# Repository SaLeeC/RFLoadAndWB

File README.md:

# RFLoadAndWB
A board to have a low power Variable Z Load and a RF Wheatstone Bridge

The intention is to make a small card (under 10 X 10 cm) that provides a dummy load (low power) with variable impedance between 5 and 2555 Ohm programmable in 5 Ohm steps and, at the same time, a Weathston Bridge which works in direct current and in RF to measure the unknown Z always in the range between 5 and 2555 Ohm.

The project is based on the following finished functional blocks:

a) Variable Z dummy load

b) Reference divider for the Weathston Bridge

c) Constant Current Generator

d) RF-DC converter for the measurement of the incoming Radio Frequency level

e) RF-DC converter for measuring the level of the reference Radio Frequency for the Weathston Bridge

f) RF-DC converter for measuring the level across the Unknown Impedance

g) Comparator for the comparison between the reference and the level at the ends of the Unknown Impedance

h) LED display for the representation of the board status (including the result of the comparison)

i) IIC interface for setting the operating parameters

All modules are finished units so they can be assembled, tested and used separately from each other.

For its operation, the board does not require a microcontroller, PC, software or other devilry, it only requires a series of switches or jumpers with which we can manually set all the operating parameters.

For the measurements a tester or a multimeter is sufficient because all the measured values are converted into Direct Current.

For direct current resistance measurements, the unknown resistor is powered by a 1 mA constant current pump allowing to read its value in Ohm directly in mV.

It is also possible to connect the card to a microcontroller through the interface module in IIC (I2C).

As for the measured values, these are converted into Direct Current and can assume values between 0 and 3.3V allowing easy interfacing with the Analog-Digital converters which are normally equipped with microcontrollers.

The comparator output is digital information and assumes the values of 0 or 3.3V

All the elements that make up the Dummy Load are 1W SMD resistors for which 1W is assumed as the maximum applicable power, in fact, since only the value of 10 Ohm is obtained with a single resistor, if really necessary, it will be possible to apply higher powers in function of the set value. This operation can irreversibly damage the load if during use combinations are chosen that are not able to withstand the applied power. In any case it is recommended not to apply more than 2W.

Inside the board hare present a free Op Amp with minimum circuit usable with Inp+ Inp- and Out for integration and experimental use

All schematics and PCB design are provided in KiCad format

The software is developed with Visual Studio Code through the PlatformIo App and is compatible with the "Arduino" environment

Mechanical drawings are produced with FreeCad.

# RFLoadAndWB
Una scheda che faccia da Carico Fittizio ad Impedenza Variabile e da Ponte di Weathston in RF

l'intenzione è quella di realizzare una piccola scheda (sotto i 10 X 10 cm) che fornisca un carico fittizio (bassa potenza) con impedenza variabile tra 5 e 2555 Ohm programmabile in step di 5 Ohm e, allo stesso tempo, un Weathston Bridge che funzioni in in corrente continua e in RF per misurare lo Z sconosciuto sempre nel range tra 5 e 2555 Ohm.

Il progetto è basato sui seguenti blocchi funzionali finiti:

a) Carico fittizio a Z variabile

b) Partitore di riferimento per il Ponte di Weathston

c) Generatore di Corrente Costante

d) Convertitore RF-DC per la misura del livello della Radio Frequenza in ingresso

e) Convertitore RF-DC per la misura del livello della Radio Frequenza di riferimento per il Ponte di Weathston

f) Convertitore RF-DC per la misura del livello ai capi della Impedenza Incognita

g) Comparatore per il confronto fra il riferimento e il livello ai capi della Impedenza Incognita

h) Display a LED per la rappresentazione dello stato della scheda (compreso il risultato della comparazione)

i) Interfaccia IIC per l'impostazione dei parametri di funzionamento

Tutti i moduli sono unità finite per cui possono essere assemblati, testati e usati separatamente uno dall'altro. 

Per il suo funzionamento la scheda non necessita di microcontrollore, PC, software o altre diavolerie, richiede solo una serie di interruttori o ponticelli con i quali possiamo manualmente impostare tutti i parametri di funzionamento.

Per le misure è sufficiente un tester o un multimetro perchè tutti i valori misurati sono convertiti in Corrente Continua.

Per le misure di resistenza in Corrente Continua la resistenza incognita è alimentata con una pompa di corrente costante da 1 mA permettendo di leggerne il valore in Ohm direttamente in mV.

E' altresì possibile collegare la scheda ad un microcontrollore tramite il modulo di interfacciamento in IIC (I2C).

Per quanto riguarda i valori misurati, questi sono convertiti in Corrente Continua e possono assumere valori compresi fra 0 e 3.3V permettendo un agevole interfacciamento con i convertitori Analogico Digitali di cui normalmente sono dotati i microcontrollori.

L'uscita del comparatore è una informazione digitale ed assume i valori di 0 o 3.3V

Tutti gli elementi che compongono il Carico Fittizio sono resistenze SMD da 1W per cui si assume 1W come potenza massima applicabile, in effetti, siccome solo il valore di 10 Ohm è ottenuto con una sola resistenza, se realmente necessario,sarà possibile applicare potenze maggiori  in funzione del valore impostato. Questa operazione può danneggiare irreversibilmente il carico se durante l'uso si scelgono combinazioni che non siano in grado di sopportare la potenza applicata. In ogni caso si consiglia di non applicare più di 2W.

All'interno della scheda è presente un Op Amp circuitato con i componenti minimi e utilizzabile tramite i pin Inp+ Inp- e Out, da usare per integrazioni o esperimenti.

Tutti gli schemi e il progetto del PCB sono forniti in formato KiCad

Il software è sviluppato con Visual Studio Code tramite l'App PlatformIo ed è compatibile con l'ambiente "Arduino"

I disegni meccanici sono prodotti con FreeCad.

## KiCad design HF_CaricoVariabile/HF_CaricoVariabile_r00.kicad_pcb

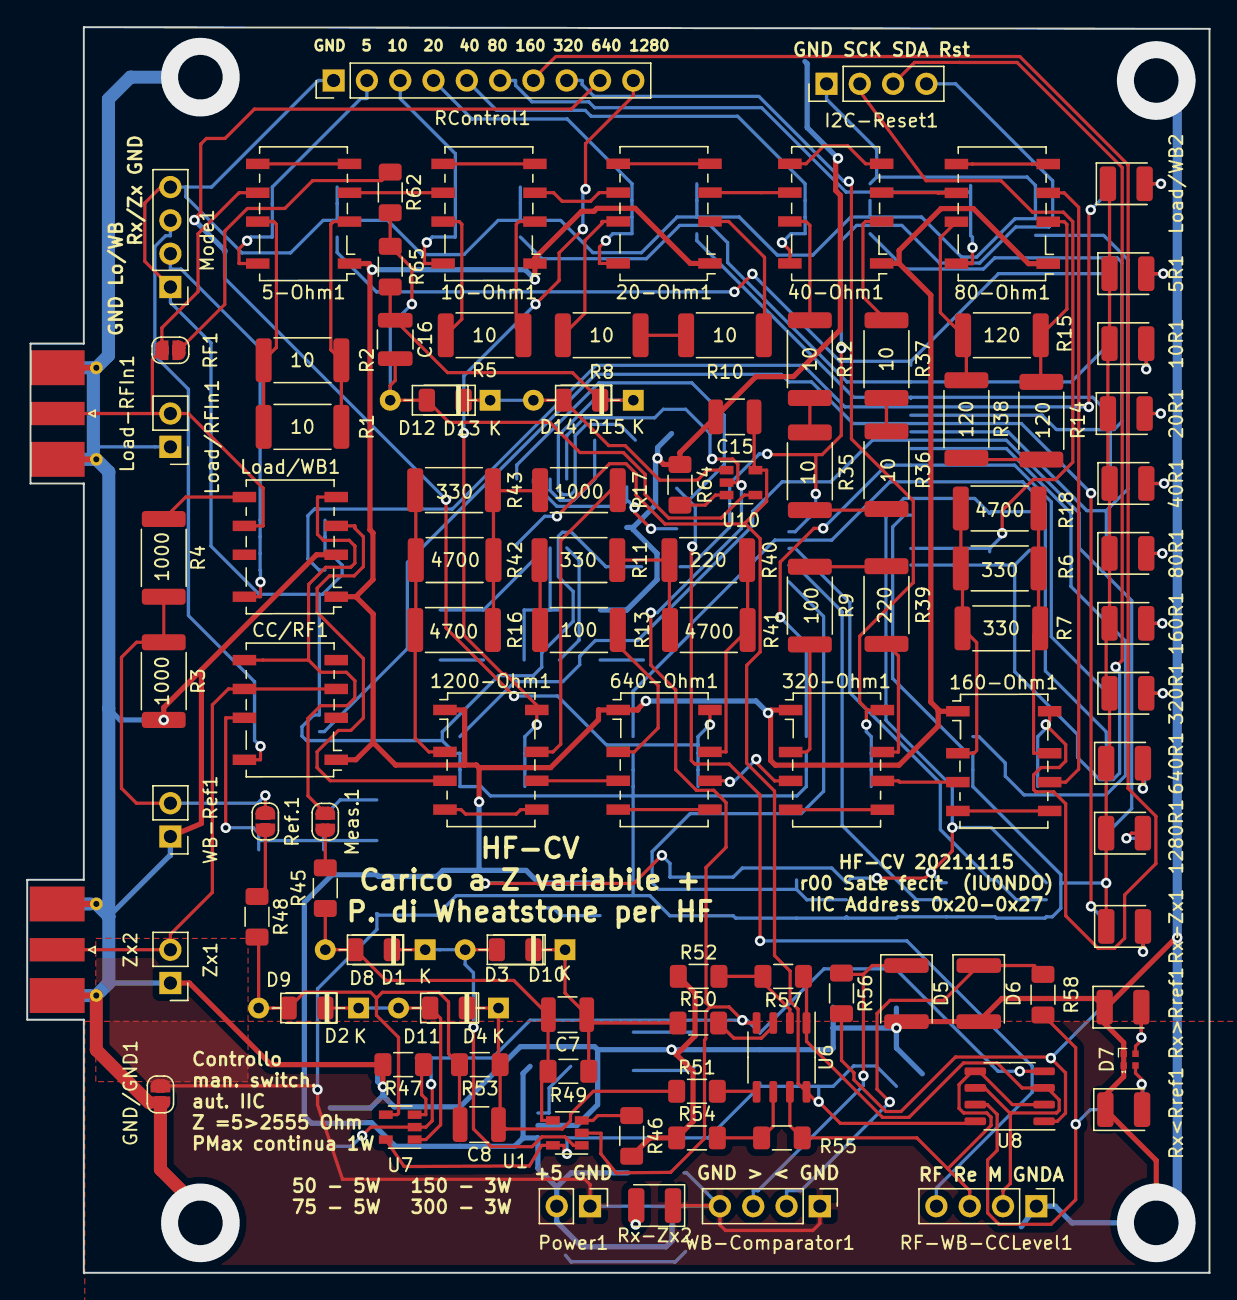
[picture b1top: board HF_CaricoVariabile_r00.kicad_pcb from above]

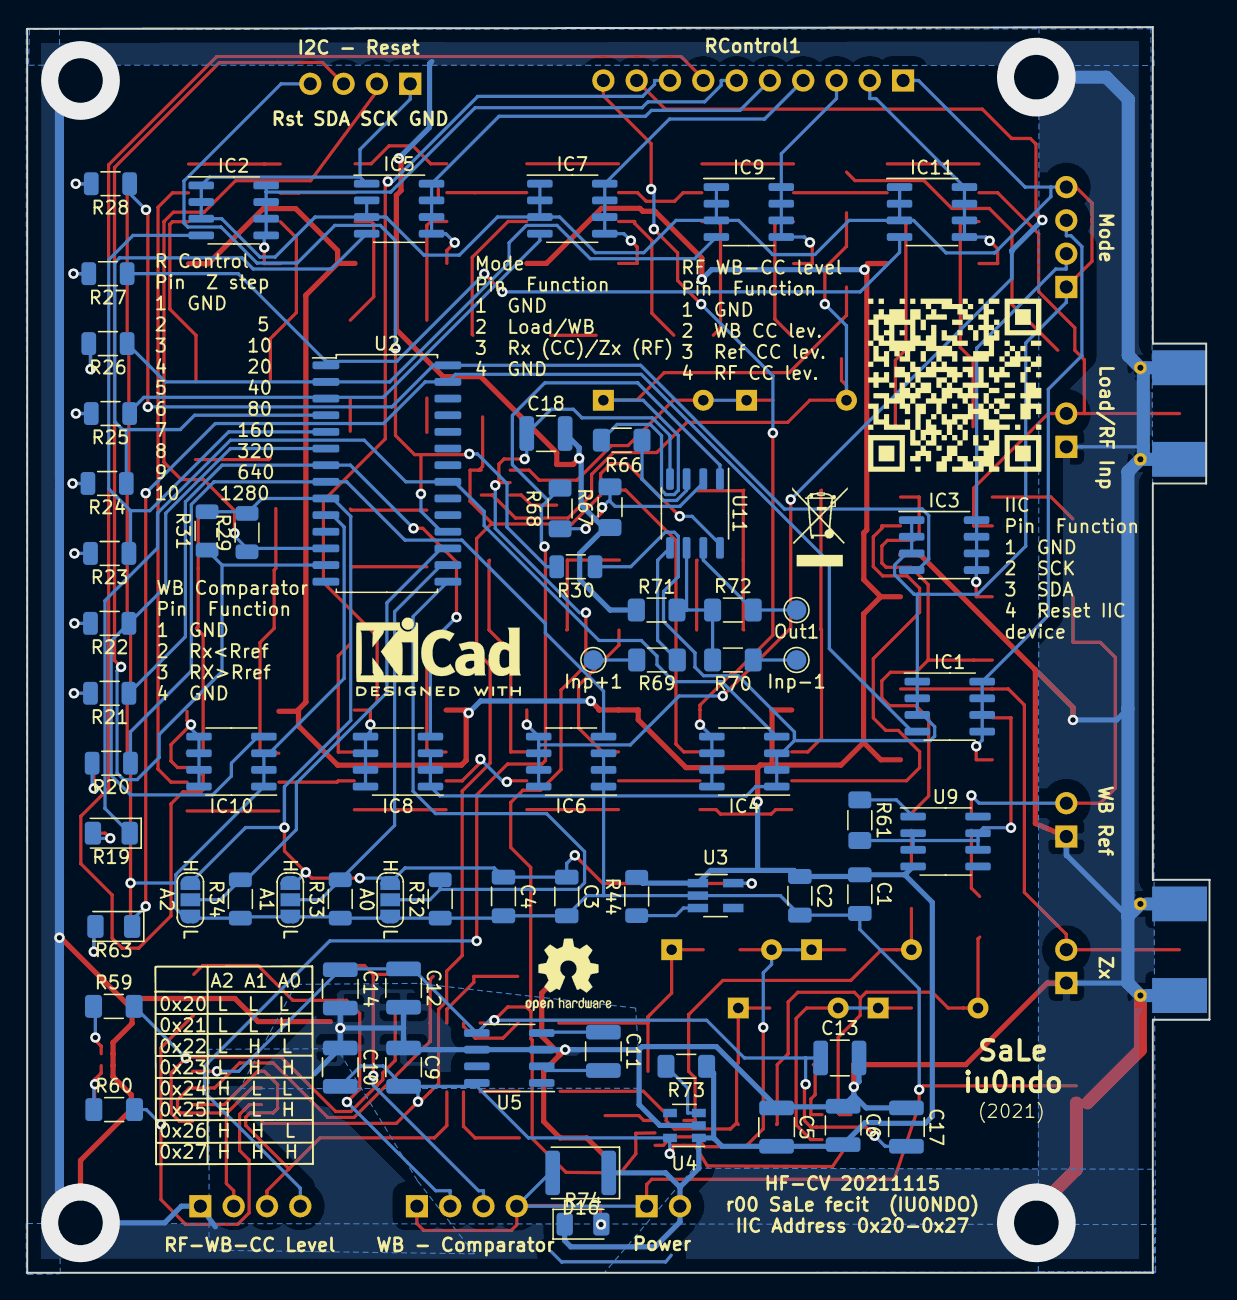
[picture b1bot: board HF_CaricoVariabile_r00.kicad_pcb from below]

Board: 2 copper layers, 90.2 x 95.0 mm, 177 parts (69 on the bottom side), 137 nets.

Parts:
5-Ohm1: 5 Ohm; Relay_DPDT_Omron_G6K-2F-Y
5R1, 10R1, 20R1, 40R1, 80R1, 160R1, 320R1, 640R1, 1280R1: LED; LED_1210_3225Metric
10-Ohm1: 10 Ohm; Relay_DPDT_Omron_G6K-2F-Y
20-Ohm1: 20 Ohm; Relay_DPDT_Omron_G6K-2F-Y
40-Ohm1: 40 Ohm; Relay_DPDT_Omron_G6K-2F-Y
80-Ohm1: 80 Ohm; Relay_DPDT_Omron_G6K-2F-Y
160-Ohm1: 160 Ohm; Relay_DPDT_Omron_G6K-2F-Y
320-Ohm1: 320 Ohm; Relay_DPDT_Omron_G6K-2F-Y
640-Ohm1: 640 Ohm; Relay_DPDT_Omron_G6K-2F-Y
1200-Ohm1: 1200 Ohm; Relay_DPDT_Omron_G6K-2F-Y
A0, A1, A2: Jumper_3_Open; SolderJumper-3_P1.3mm_Open_RoundedPad1.0x1.5mm_NumberLabels
C1, C2, C3, C4: C; C_1206_3216Metric
C5, C9, C12: 100u; R_1210_3225Metric
C6, C7, C8, C10, C14, C16: 100n; R_1210_3225Metric
C11: 10u; R_1210_3225Metric
C13, C15, C17, C18: 10n; R_1210_3225Metric
CC/RF1: CC-RF; Relay_DPDT_Omron_G6K-2F-Y
D1, D2, D3, D4, D12, D15: 1N4148; D_DO-35_SOD27_P7.62mm_Horizontal
D5, D6, D16: SD12; D_1812_4532Metric
D7: LED_Dual_CACA; LED_SK6812_EC15_1.5x1.5mm
D8, D9, D10, D11, D13, D14: 1N4148; D_1206_3216Metric
GND/GND1: GND/GND; SolderJumper-2_P1.3mm_Open_RoundedPad1.0x1.5mm
I2C-Reset1: Conn_01x04_Female; PinHeader_1x04_P2.54mm_Vertical
IC1, IC2, IC3, IC4, IC5, IC6, IC7, IC8, IC9, IC10, IC11: STS6NF20V; SOIC-8_3.9x4.9mm_P1.27mm
Inp+1: TestPoint; TestPoint_Pad_D1.5mm
Inp-1: TestPoint; TestPoint_Pad_D1.5mm
Load-RFIn1: Load/RFin; SMA_Molex_73251-2120_EdgeMount_Horizontal
Load/RFIn1: Load/RFIn; PinHeader_1x02_P2.54mm_Vertical
Load/WB1: 5 Ohm; Relay_DPDT_Omron_G6K-2F-Y
Load/WB2: LED; LED_1210_3225Metric
Meas.1: Jumper_2_Open; SolderJumper-2_P1.3mm_Open_RoundedPad1.0x1.5mm
Mode1: Conn_01x04_Female; PinHeader_1x04_P2.54mm_Vertical
Out1: TestPoint; TestPoint_Pad_D1.5mm
Power1: Conn_01x02_Female; PinHeader_1x02_P2.54mm_Vertical
QR*****: HF_CaricoVaribile_QR-Code-Piccolo-r00
R1, R2, R5, R8, R10, R12, R35, R36, R37: 10; R_2512_6332Metric
R3, R4, R17: 1000; R_2512_6332Metric
R6, R7, R11, R42: 330; R_2512_6332Metric
R9, R13: 100; R_2512_6332Metric
R14, R15, R38: 120; R_2512_6332Metric
R16, R18, R41, R43: 4700; R_2512_6332Metric
R19, R63, R74: R; LED_1206_3216Metric
R20, R21, R22, R23, R24, R25, R26, R27, R28, R29, R30, R31, R32, R33, R34, R44: R; R_1206_3216Metric
R39, R40: 220; R_2512_6332Metric
R45, R48, R50, R51, R62, R66, R69, R70, R71, R72, R73: 100K; R_1206_3216Metric_Pad1.30x1.75mm_HandSolder
R46, R47, R64: 47K; R_1206_3216Metric_Pad1.30x1.75mm_HandSolder
R49, R53, R65: 220K; R_1206_3216Metric_Pad1.30x1.75mm_HandSolder
R52, R54, R55, R56, R58, R67: 10K; R_1206_3216Metric_Pad1.30x1.75mm_HandSolder
R57, R68: 10k; R_1206_3216Metric_Pad1.30x1.75mm_HandSolder
R59, R60: 100; R_1206_3216Metric_Pad1.30x1.75mm_HandSolder
R61: 68; R_1206_3216Metric_Pad1.30x1.75mm_HandSolder
RControl1: Conn_01x10_Female; PinHeader_1x10_P2.54mm_Vertical
RF1: Jumper_2_Open; SolderJumper-2_P1.3mm_Open_RoundedPad1.0x1.5mm
RF-WB-CCLevel1: Conn_01x04_Female; PinHeader_1x04_P2.54mm_Vertical
Ref.1: Jumper_2_Open; SolderJumper-2_P1.3mm_Open_RoundedPad1.0x1.5mm
Rx-Zx1, Rx-Zx2: LED; LED_1210_3225Metric
Rx<Rref1: LED; LED_1210_3225Metric
Rx>Rref1: LED; LED_1210_3225Metric
U1, U7, U10: OPA356; SOT-23-5
U2: MCP23017_SO; SOIC-28W_7.5x17.9mm_P1.27mm
U3: TLV70033_SOT23-5; SOT-23-5_HandSoldering
U4: TLV70033_SOT23-5; SOT-23-5
U5: ICL7660; SOIC-8_3.9x4.9mm_P1.27mm
U6, U8, U11: TL072; SOP-8_3.9x4.9mm_P1.27mm
U9: LM334M; SOIC-8_3.9x4.9mm_P1.27mm
WB-Comparator1: Conn_01x04_Female; PinHeader_1x04_P2.54mm_Vertical
WB-Ref1: RFRef; PinHeader_1x02_P2.54mm_Vertical
Zx1: Zx; PinHeader_1x02_P2.54mm_Vertical
Zx2: Zx; SMA_Molex_73251-2120_EdgeMount_Horizontal

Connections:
+3.3VP: A0.3, A1.3, A2.3, C3.1, C4.1, R29.2, R31.2, U2.9, U3.5
+3V3: C9.2, C10.2, C15.1, U1.5, U4.5, U5.8, U6.8, U7.5, U8.8, U10.5, U11.8
+5V: 5-Ohm1.1, 10-Ohm1.1, 20-Ohm1.1, 40-Ohm1.1, 80-Ohm1.1, 160-Ohm1.1, 320-Ohm1.1, 640-Ohm1.1, 1200-Ohm1.1, C1.1, C2.1, C5.2, C6.2, CC/RF1.1, D16.1, Load/WB1.1, Power1.2, R44.2, R73.1, R74.1, U3.1, U4.1, U9.4
-3V3: C12.2, C13.1, C14.2, C17.1, C18.1, U1.2, U5.5, U6.4, U7.2, U8.4, U10.2, U11.4
/HFCaricoVariabile-Load/1mACC: CC/RF1.7, R61.2, U9.2, U9.3, U9.6, U9.7
/HFCaricoVariabile-Load/GND-WB: 1200-Ohm1.3, Load/WB1.3
/HFCaricoVariabile-Load/HF Carico Variabile Differential OpAmp Measure/RFLevel: 5-Ohm1.6, Load-RFIn1.1, Load/RFIn1.2, Load/WB1.6, RF1.1
/HFCaricoVariabile-Load/HF Carico Variabile Differential OpAmp Measure/WB-Measu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: CC/RF1.5, Load/WB1.4, Meas.1.1
/HFCaricoVariabile-Load/HF Carico Variabile Differential OpAmp Measure/WB-Refer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: R3.1, R4.2, Ref.1.1, WB-Ref1.2
/HFCaricoVariabile-Load/RFLevel-Out: R68.1, RF-WB-CCLevel1.4, U11.1
/HFCaricoVariabile-Load/RL0005: 5-Ohm1.8, IC11.5, IC11.6, IC11.7, IC11.8, RControl1.2
/HFCaricoVariabile-Load/RL0010: 10-Ohm1.8, IC9.5, IC9.6, IC9.7, IC9.8, RControl1.3
/HFCaricoVariabile-Load/RL0020: 20-Ohm1.8, IC7.5, IC7.6, IC7.7, IC7.8, RControl1.4
/HFCaricoVariabile-Load/RL0040: 40-Ohm1.8, IC5.5, IC5.6, IC5.7, IC5.8, RControl1.5
/HFCaricoVariabile-Load/RL0080: 80-Ohm1.8, IC2.5, IC2.6, IC2.7, IC2.8, RControl1.6
/HFCaricoVariabile-Load/RL0160: 160-Ohm1.8, IC10.5, IC10.6, IC10.7, IC10.8, RControl1.7
/HFCaricoVariabile-Load/RL0320: 320-Ohm1.8, IC8.5, IC8.6, IC8.7, IC8.8, RControl1.8
/HFCaricoVariabile-Load/RL0640: 640-Ohm1.8, IC6.5, IC6.6, IC6.7, IC6.8, RControl1.9
/HFCaricoVariabile-Load/RL1200: 1200-Ohm1.8, IC4.5, IC4.6, IC4.7, IC4.8, RControl1.10
/HFCaricoVariabile-Load/RLLoad-WB: IC3.5, IC3.6, IC3.7, IC3.8, Load/WB1.8, Mode1.2
/HFCaricoVariabile-Load/RLRx-Zx: CC/RF1.8, IC1.5, IC1.6, IC1.7, IC1.8, Mode1.3
/HFCaricoVariabile-Load/Rx<Rref: D6.1, R58.2, WB-Comparator1.2
/HFCaricoVariabile-Load/Rx>Rref: D5.1, R56.1, WB-Comparator1.3
/HFCaricoVariabile-Load/WB-MeasureOut: R57.1, RF-WB-CCLevel1.2, U6.1, U8.3, U8.6
/HFCaricoVariabile-Load/WB-ReferenceOut: R55.1, RF-WB-CCLevel1.3, U6.7, U8.2, U8.5
/HFCaricoVariabile-ReleDriver/RL-RESET: I2C-Reset1.4, R30.2, U2.18
/HFCaricoVariabile-ReleDriver/RL-SCK: I2C-Reset1.2, R29.1, U2.12
/HFCaricoVariabile-ReleDriver/RL-SDA: I2C-Reset1.3, R31.1, U2.13
GND: 5R1.1, 10R1.1, 20R1.1, 40R1.1, 80R1.1, 160R1.1, 320R1.1, 640R1.1, 1280R1.1, A0.1, A1.1, A2.1, C1.2, C2.2, C3.2, C4.2, D16.2, GND/GND1.2, I2C-Reset1.1, IC1.1, IC1.2, IC1.3, IC2.1, IC2.2, IC2.3, IC3.1, IC3.2, IC3.3, IC4.1, IC4.2, IC4.3, IC5.1, IC5.2, IC5.3, IC6.1, IC6.2, IC6.3, IC7.1, IC7.2, IC7.3, IC8.1, IC8.2, IC8.3, IC9.1, IC9.2, IC9.3, IC10.1, IC10.2, IC10.3, IC11.1, IC11.2, IC11.3, Load/WB2.1, Mode1.1, Mode1.4, Power1.1, R30.1, R32.1, R33.1, R34.1, RControl1.1, Rx-Zx1.1, Rx-Zx2.1, U2.10, U3.2, WB-Comparator1.1, WB-Comparator1.4
GNDA: C5.1, C6.1, C9.1, C10.1, C12.1, C13.2, C14.1, C15.2, C17.2, C18.2, D5.2, D6.2, D7.1, D7.4, GND/GND1.1, Load-RFIn1.2, Load/RFIn1.1, Load/WB1.2, R3.2, R46.2, R47.2, R52.1, R54.1, R64.2, R67.1, R71.2, RF-WB-CCLevel1.1, Rx<Rref1.1, Rx>Rref1.1, U4.2, U5.3, U5.6, WB-Ref1.1, Zx1.1, Zx2.2
unnamed: 5-Ohm1.2, R1.1, R2.1
unnamed: 5-Ohm1.4, 5-Ohm1.5
unnamed: 5-Ohm1.7, R1.2, R2.2
unnamed: 5R1.2, R27.2
unnamed: 10-Ohm1.2, R5.1
unnamed: 10-Ohm1.3, 20-Ohm1.6
unnamed: 10-Ohm1.4, 10-Ohm1.5
unnamed: 5-Ohm1.3, 10-Ohm1.6
unnamed: 10-Ohm1.7, R5.2
unnamed: 10R1.2, R26.2
unnamed: 20-Ohm1.2, R10.2
unnamed: 20-Ohm1.3, 40-Ohm1.6
unnamed: 20-Ohm1.4, 20-Ohm1.5
unnamed: 20-Ohm1.7, R8.2
unnamed: 20R1.2, R25.2
unnamed: 40-Ohm1.2, R37.2
unnamed: 40-Ohm1.3, 80-Ohm1.6
unnamed: 40-Ohm1.4, 40-Ohm1.5
unnamed: 40-Ohm1.7, R12.2
unnamed: 40R1.2, R24.2
unnamed: 80-Ohm1.2, R14.2, R15.1
unnamed: 80-Ohm1.4, 80-Ohm1.5
unnamed: 80-Ohm1.7, R15.2, R38.2
unnamed: 80R1.2, R23.2
unnamed: 160-Ohm1.2, R6.1, R7.1, R18.1
unnamed: 160-Ohm1.3, 320-Ohm1.6
unnamed: 160-Ohm1.4, 160-Ohm1.5
unnamed: 80-Ohm1.3, 160-Ohm1.6
unnamed: 160-Ohm1.7, R6.2, R7.2, R18.2
unnamed: 160R1.2, R22.2
unnamed: 320-Ohm1.2, R9.2
unnamed: 320-Ohm1.3, 640-Ohm1.6
unnamed: 320-Ohm1.4, 320-Ohm1.5
unnamed: 320-Ohm1.7, R39.2
unnamed: 320R1.2, R21.2
unnamed: 640-Ohm1.2, R13.2
unnamed: 640-Ohm1.4, 640-Ohm1.5
unnamed: 640-Ohm1.7, R40.2, R41.2
unnamed: 640R1.2, R20.2
unnamed: 1200-Ohm1.2, R16.1, R42.2, R43.1
unnamed: 1200-Ohm1.4, 1200-Ohm1.5
unnamed: 640-Ohm1.3, 1200-Ohm1.6
unnamed: 1200-Ohm1.7, R17.2
unnamed: 1280R1.2, R19.2
unnamed: A0.2, R32.2, U2.15
unnamed: A1.2, R33.2, U2.16
unnamed: A2.2, R34.2, U2.17
unnamed: C7.1, D3.1, D10.1, R49.1, R50.1
unnamed: C7.2, D1.2, D8.2, R45.2, R49.2, U1.4
unnamed: C8.1, D4.1, D11.1, R51.1, R53.1
unnamed: C8.2, D2.2, D9.2, R48.2, R53.2, U7.4
unnamed: C11.1, U5.4
unnamed: C11.2, U5.2
unnamed: C16.1, D14.1, D15.1, R65.1, R66.1
unnamed: C16.2, D12.2, D13.2, R62.2, R65.2, U10.4
unnamed: CC/RF1.3, CC/RF1.6, Zx1.2, Zx2.1
unnamed: D1.1, D3.2, D8.1, D10.2, U1.1
unnamed: D7.2, R60.1, Rx<Rref1.2
unnamed: D7.3, R59.1, Rx>Rref1.2
unnamed: D2.1, D4.2, D9.1, D11.2, U7.1
unnamed: D12.1, D13.1, D14.2, D15.2, U10.1
unnamed: IC1.4, R63.1, U2.27
unnamed: IC2.4, R23.1, U2.5
unnamed: IC3.4, R28.1, U2.28
unnamed: IC4.4, R19.1, U2.21
unnamed: IC5.4, R24.1, U2.4
unnamed: IC6.4, R20.1, U2.8
unnamed: IC7.4, R25.1, U2.3
unnamed: IC8.4, R21.1, U2.7
unnamed: IC9.4, R26.1, U2.2
unnamed: IC10.4, R22.1, U2.6
unnamed: IC11.4, R27.1, U2.1
unnamed: Inp+1.1, R69.1
unnamed: Inp-1.1, R70.1
unnamed: Load/WB1.5, R4.1
unnamed: Load/WB2.2, R28.2
unnamed: Meas.1.2, R45.1
unnamed: Out1.1, R72.2, U11.7
unnamed: R8.1, R10.1
unnamed: R11.1, R40.1, R41.1
unnamed: R11.2, R13.1
unnamed: R12.1, R35.2
unnamed: R14.1, R38.1
unnamed: R16.2, R17.1, R42.1, R43.2
unnamed: R35.1, R36.2
unnamed: R36.1, R37.1
unnamed: R9.1, R39.1
unnamed: R44.1, U3.3
unnamed: R46.1, U1.3
unnamed: R47.1, U7.3
unnamed: R48.1, Ref.1.2
unnamed: R50.2, U6.3
unnamed: R51.2, U6.5
unnamed: R52.2, R57.2, U6.2
unnamed: R54.2, R55.2, U6.6
unnamed: R56.2, R59.2, U8.1
unnamed: R58.1, R60.2, U8.7
unnamed: R61.1, U9.1
unnamed: R62.1, RF1.2
unnamed: R63.2, Rx-Zx1.2
unnamed: R64.1, U10.3
unnamed: R66.2, U11.3
unnamed: R67.2, R68.2, U11.2
unnamed: R69.2, U11.5
unnamed: R70.2, R71.1, R72.1, U11.6
unnamed: R73.2, U4.3
unnamed: R74.2, Rx-Zx2.2

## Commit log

2021-11-30 Create Note
